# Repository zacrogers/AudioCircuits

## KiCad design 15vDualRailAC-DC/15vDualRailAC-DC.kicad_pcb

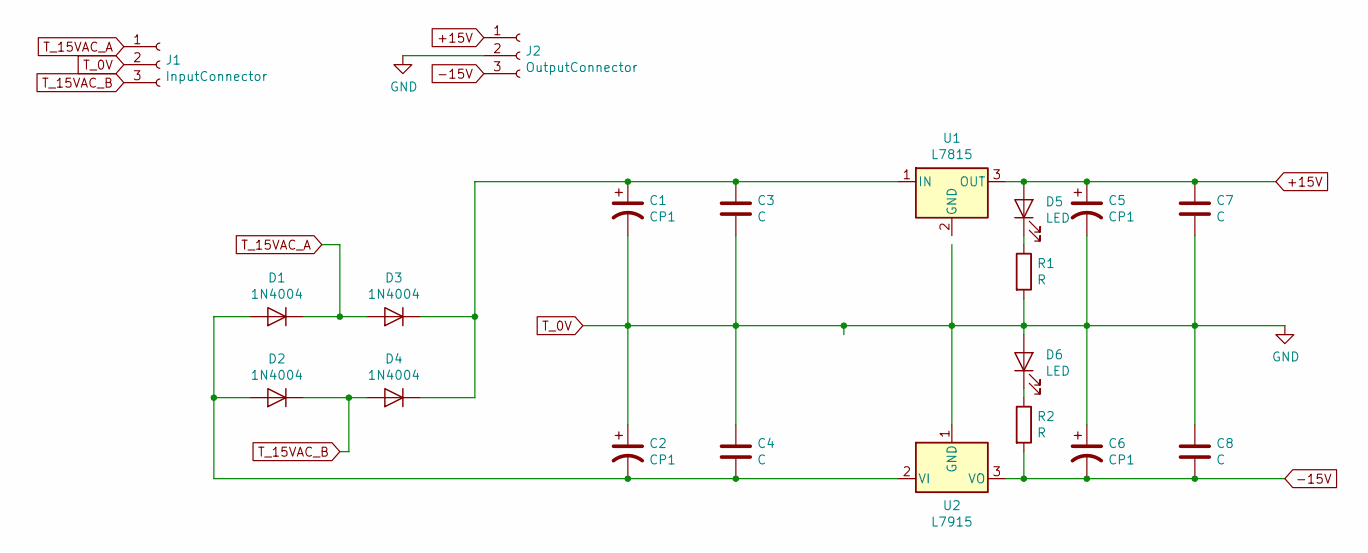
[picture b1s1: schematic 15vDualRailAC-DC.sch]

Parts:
C1, C2, C5, C6: CP1; CP_Radial_D10.0mm_P5.00mm
C3, C4, C7, C8: C; C_Disc_D6.0mm_W2.5mm_P5.00mm
D1, D2, D3, D4: 1N4004; D_DO-41_SOD81_P10.16mm_Horizontal
D5, D6: LED; LED_D5.0mm
J1: InputConnector; TerminalBlock_Altech_AK300-3_P5.00mm
J2: OutputConnector; TerminalBlock_Altech_AK300-3_P5.00mm
R1, R2: R; R_Axial_DIN0411_L9.9mm_D3.6mm_P12.70mm_Horizontal
U1: L7815; TO-220-3_Vertical
U2: L7915; TO-220-3_Vertical

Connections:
+15V: C5.1, C7.1, D5.2 (A), J2.1, U1.3 (OUT)
-15V: C6.2, C8.2, J2.3, R2.2, U2.3 (VO)
unnamed: C1.1, C3.1, D3.1 (K), D4.1 (K), U1.1 (IN)
unnamed: C2.2, C4.2, D1.2 (A), D2.2 (A), U2.2 (VI)
unnamed: D5.1 (K), R1.1
unnamed: D6.1 (K), R2.1
T_0V: C1.2, C2.1, C3.2, C4.1, C5.2, C6.1, C7.2, C8.1, D6.2 (A), J1.2, J2.2, R1.2, U2.1 (GND)
T_15VAC_A: D1.1 (K), D3.2 (A), J1.1
T_15VAC_B: D2.1 (K), D4.2 (A), J1.3

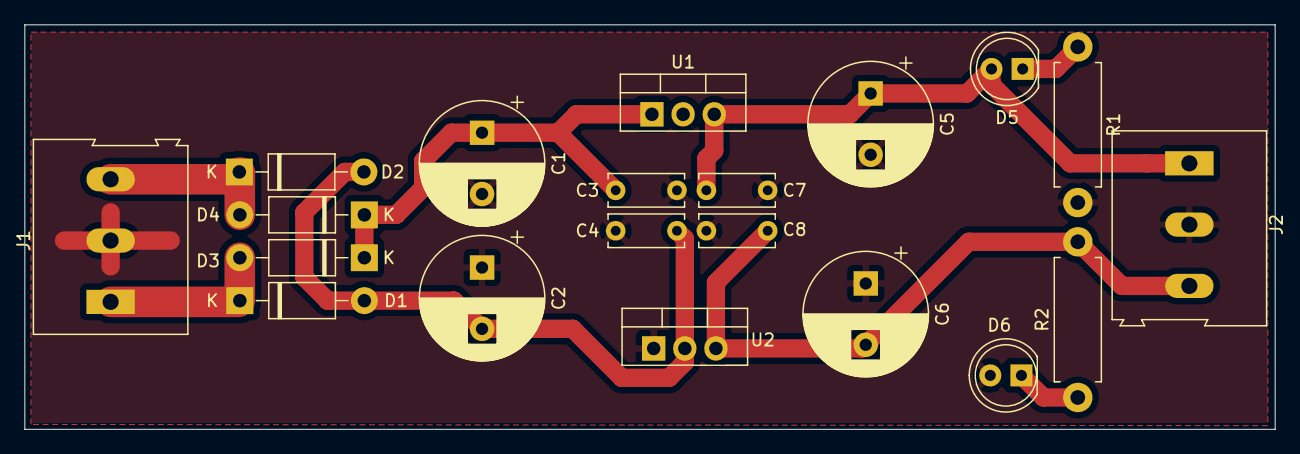
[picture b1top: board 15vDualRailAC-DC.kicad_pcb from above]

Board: 2 copper layers, 102.0 x 33.0 mm, 20 parts (0 on the bottom side), 9 nets.

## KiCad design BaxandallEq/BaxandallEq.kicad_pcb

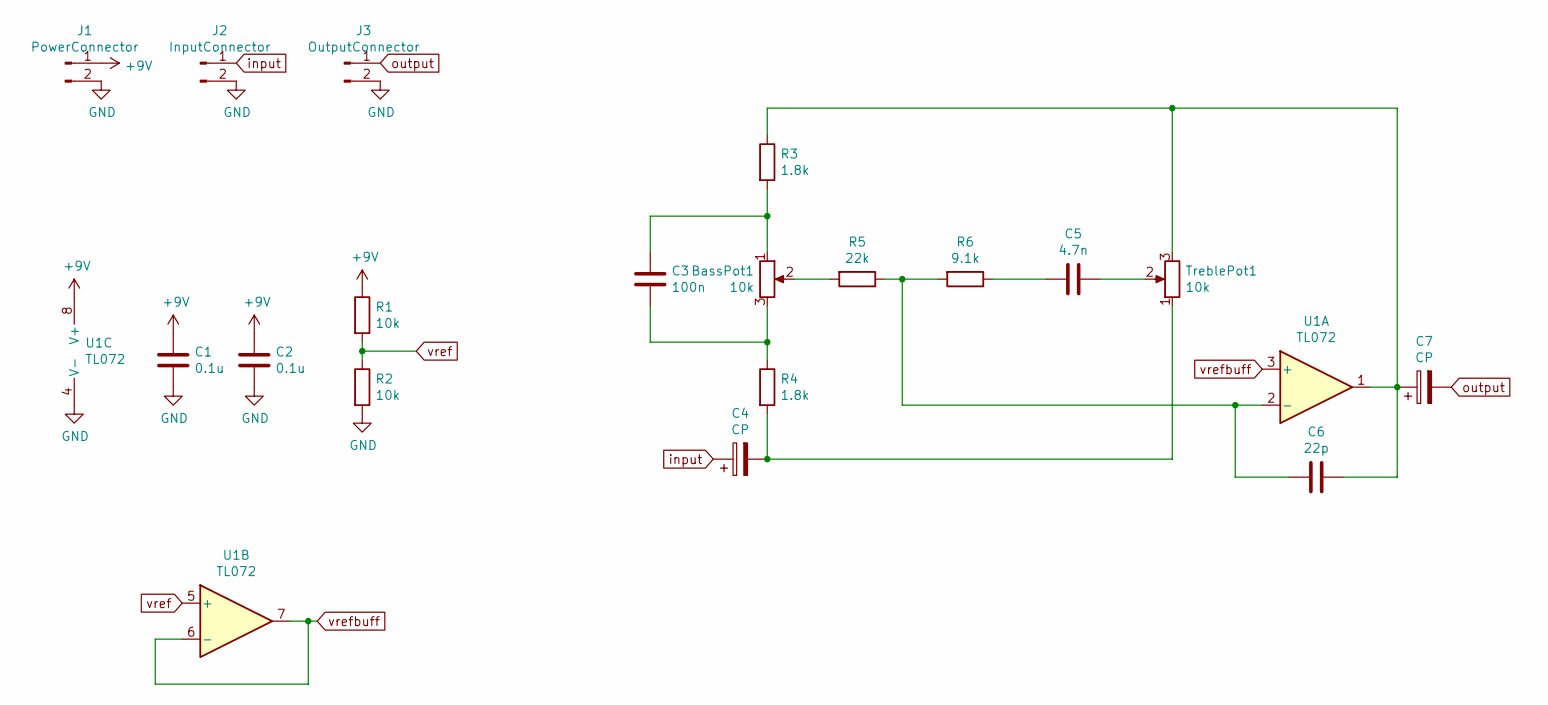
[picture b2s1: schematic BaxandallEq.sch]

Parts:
BassPot1: 10k; Potentiometer_Alps_RK097_Single_Horizontal
C1, C2: 0.1u; C_1206_3216Metric
C3: 100n; C_1206_3216Metric
C4, C7: CP; CP_Radial_D6.3mm_P2.50mm
C5: 4.7n; C_1206_3216Metric
C6: 22p; C_1206_3216Metric
J1: PowerConnector; PinHeader_1x02_P2.54mm_Vertical
J2: InputConnector; PinHeader_1x02_P2.54mm_Vertical
J3: OutputConnector; PinHeader_1x02_P2.54mm_Vertical
R1, R2: 10k; R_1206_3216Metric
R3, R4: 1.8k; R_1206_3216Metric
R5: 22k; R_1206_3216Metric
R6: 9.1k; R_1206_3216Metric
TreblePot1: 10k; Potentiometer_Alps_RK097_Single_Horizontal
U1: TL072; DIP-8_W7.62mm

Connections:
+9V: C1.1, C2.1, J1.1, R1.1, U1.8 (V+)
GND: C1.2, C2.2, J1.2, J2.2, J3.2, R2.2, U1.4 (V-)
unnamed: BassPot1.1, C3.1, R3.2
unnamed: BassPot1.2, R5.2
unnamed: BassPot1.3, C3.2, R4.1
unnamed: C4.2, R4.2, TreblePot1.1
unnamed: C5.1, TreblePot1.2
unnamed: C5.2, R6.1
unnamed: C6.1, C7.1, R3.1, TreblePot1.3, U1.1
unnamed: C6.2, R5.1, R6.2, U1.2 (-)
input: C4.1, J2.1
output: C7.2, J3.1
vref: R1.2, R2.1, U1.5 (+)
vrefbuff: U1.3 (+), U1.6 (-), U1.7

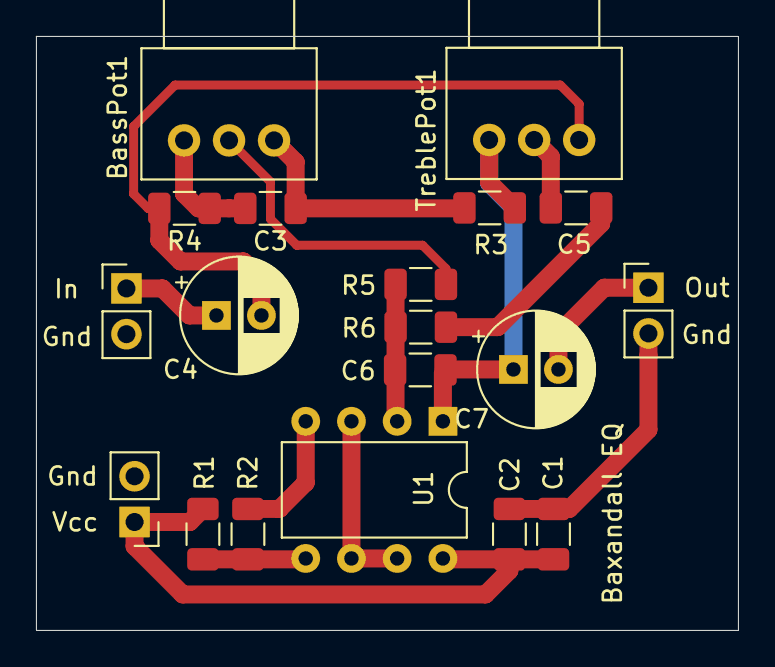
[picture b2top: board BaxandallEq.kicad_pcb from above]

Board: 2 copper layers, 39.0 x 33.0 mm, 19 parts (0 on the bottom side), 14 nets.

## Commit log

2021-08-23 Added kicad projects
2021-08-23 Added psu kicad project
